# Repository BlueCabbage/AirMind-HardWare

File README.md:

Hardware
========

PX4 Hardware designs

Website at: http://pixhawk.org

PX4 is an open hardware design, following the OSHW 1.1 definition licensed under the Creative Commons Attribution-ShareAlike 3.0 Unported (CC BY-SA 3.0) license.

Pull requests for relevant fixes are very welcome.

Pixhawk v1 Hardware
===================

FMUv1 & FMUv2 boards

Design files are EAGLE CAD files (can be viewed with the free version)
www.cadsoftusa.com/

And BOM management is performed using Bob Starr's BOM-EX plugin:
http://www.bobstarr.net/pages/downloads.html

Pixhawk v2 Hardware
===================

FMUv3 board (and IMUv3 + PSMv3 support components)

The Pixhawk v2 Hardware is the result of a collaboration of the open hardware development community and 3D Robotics and has been designed in Altium.

MindPX V2 Hardware
===================

MindPX V2 board (Hardware version:   v2.2)
http://www.mindpx.net

Product brief:
http://www.mindpx.net/assets/accessories/brochure.pdf

Hardware specification:
http://www.mindpx.net/assets/accessories/Specification_MindPX.pdf

User manual:
http://www.mindpx.net/assets/accessories/UserGuide_MindPX.pdf

Revisions against Pixhawk:

1. 6 PWM distance sensors inputs
2. 1 extra parallel I2C port (so can support external compass and px4flow simultaneously)
3. Secondary USB port  for companion computer (converted from UART2 using onboard CP2104)
4. exposed SWD debug port
5. Built-in vibration dampening, support hard mount on air frames.
6. removed in v2.2:
        • Spektrum DSM / DSM2 / DSM-X® Satellite compatible input
        • Futaba S.BUS® compatible input and output
        • auxiliary outputs
        • safety switch (moved to power distribution board as eSwitch)

Note: MindPX v2.2 supports maximum 6 direct PWM outputs.

Creative Commons License Disclaimer
===================================

UNLESS OTHERWISE MUTUALLY AGREED TO BY THE PARTIES IN WRITING, LICENSOR OFFERS THE WORK AS-IS AND MAKES NO REPRESENTATIONS OR WARRANTIES OF ANY KIND CONCERNING THE WORK, EXPRESS, IMPLIED, STATUTORY OR OTHERWISE, INCLUDING, WITHOUT LIMITATION, WARRANTIES OF TITLE, MERCHANTIBILITY, FITNESS FOR A PARTICULAR PURPOSE, NONINFRINGEMENT, OR THE ABSENCE OF LATENT OR OTHER DEFECTS, ACCURACY, OR THE PRESENCE OF ABSENCE OF ERRORS, WHETHER OR NOT DISCOVERABLE. SOME JURISDICTIONS DO NOT ALLOW THE EXCLUSION OF IMPLIED WARRANTIES, SO SUCH EXCLUSION MAY NOT APPLY TO YOU.
EXCEPT TO THE EXTENT REQUIRED BY APPLICABLE LAW, IN NO EVENT WILL LICENSOR BE LIABLE TO YOU ON ANY LEGAL THEORY FOR ANY SPECIAL, INCIDENTAL, CONSEQUENTIAL, PUNITIVE OR EXEMPLARY DAMAGES ARISING OUT OF THIS LICENSE OR THE USE OF THE WORK, EVEN IF LICENSOR HAS BEEN ADVISED OF THE POSSIBILITY OF SUCH DAMAGES.

http://creativecommons.org/licenses/by-sa/3.0/

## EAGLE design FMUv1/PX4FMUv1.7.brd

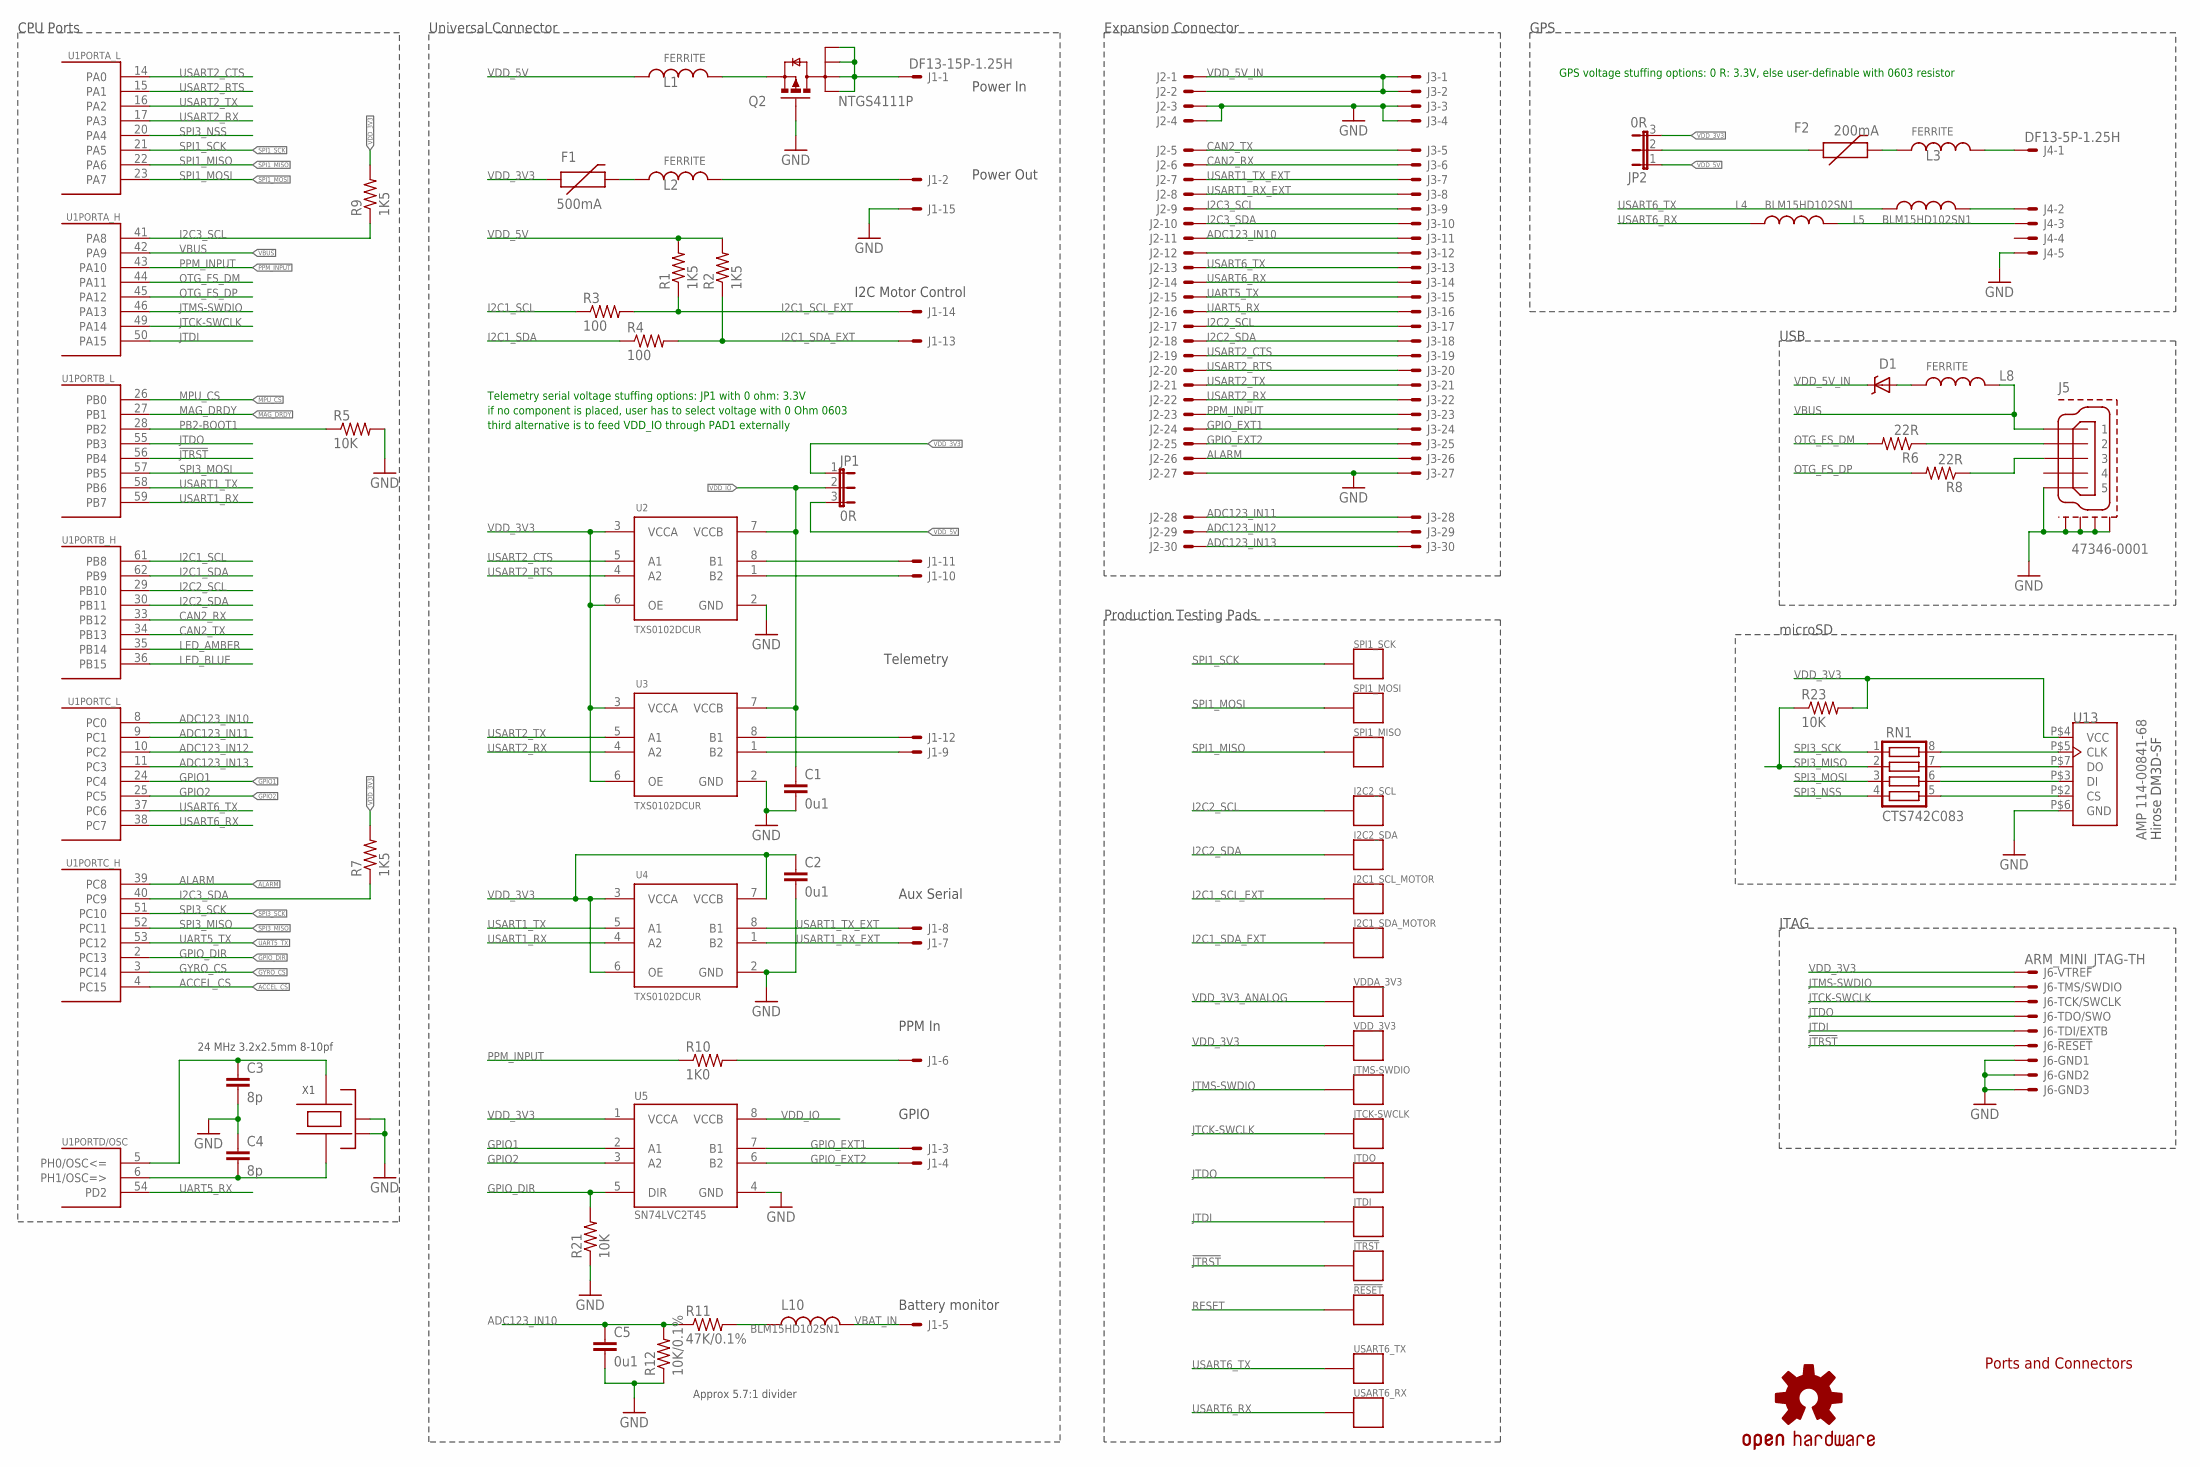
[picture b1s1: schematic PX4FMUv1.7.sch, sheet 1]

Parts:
!JTRST: PAD.04; PAD.04X.04; PARTNO *
!RESET: PAD.04; PAD.04X.04; PARTNO *
C1, C2, C5: 0u1; 0402-CAP; PARTNO CC0402ZRY5V7BB104
C3, C4: 8p; 0402-CAP; PARTNO C1005C0G1H080C
D1: MSS1P4-M3; MICROSMP; PARTNO MSS1P4-M3/89A
F1: 500mA; 0402-PTC; PARTNO MF-FSMF050X-2
F2: 200mA; 0402-PTC; PARTNO MF-FSMF020X-2
I2C1_SCL_MOTOR, I2C1_SDA_MOTOR, I2C2_SCL: PAD.03; PAD.03X.03; PARTNO *
I2C2_SDA: PAD.04; PAD.04X.04; PARTNO *
J1: DF13-15P-1.25H; DF13A-15P-1.25H; PARTNO DF13A-15P-1.25H(20)
J2: HEADER_2X15-REV; HEADER_2MM_2X15_REVERSE; PARTNO 953230-2000-AR-PR
J3: HEADER_2X15; HEADER_2MM_2X15; PARTNO 953230-2000-AR-PR
J4: DF13-5P-1.25H; DF13A-5P-1.25H; PARTNO DF13A-5P-1.25H(20)
J5: 47346-0001; MOLEX-47346-0001; PARTNO 47346-0001
J6: ARM_MINI_JTAG-TH; FTSH-105-01-XXX-DV; PARTNO M50-3900542
JP1, JP2: 0R; SJ_3_0603_PASTE1&2; PARTNO RMCF0402ZT0R00
JTCK-SWCLK: PAD.04; PAD.04X.04; PARTNO *
JTDI: PAD.04; PAD.04X.04; PARTNO *
JTDO: PAD.04; PAD.04X.04; PARTNO *
JTMS-SWDIO: PAD.04; PAD.04X.04; PARTNO *
L1, L2, L3, L8: FERRITE; 0402-IND; PARTNO BKP1005HS121-T
L4, L5, L10: BLM15HD102SN1; 0402-IND; PARTNO BLM15HD102SN1
Q2: NTGS4111P; TSOP-6; PARTNO NTGS4111P
R1, R2, R7, R9: 1K5; 0402-RES; PARTNO RMCF0402JT1K50
R3, R4: 100; 0402-RES; PARTNO RMCF0402JT100R
R5, R21, R23: 10K; 0402-RES; PARTNO RMCF0402FT10K0
R6, R8: 22R; 0402-RES; PARTNO RMCF0402JT22R0
R10: 1K0; 0402-RES; PARTNO RMCF0402JT1K00
R11: 47K/0.1%; 0402-RES; PARTNO ERA-2AEB473X
R12: 10K/0.1%; 0402-RES; PARTNO ERA-2AEB103X
RN1: CTS742C083; PARTNO TC164-JR-07100RL
SPI1_MISO, SPI1_MOSI, SPI1_SCK: PAD.04; PAD.04X.04; PARTNO *
U1: STM32F405RGT6; TQFP64; PARTNO STM32F405RGT6
U2, U3, U4: TXS0102DCUR; TI-DCU; PARTNO TXS0102DCUR
U5: SN74LVC2T45; TI-DCU; PARTNO SN74LVC2T45
U13: AMP 114-00841-68; AMPHENOL_114-00841-68; PARTNO 114-00841-68
U$7: OSHW-LOGOS; OSHW-LOGO-S; PARTNO *
USART6_RX, USART6_TX: PAD.04; PAD.04X.04; PARTNO *
VDDA_3V3: PAD.04; PAD.04X.04; PARTNO *
VDD_3V3: PAD.04; PAD.04X.04; PARTNO *
X1: 24 MHz 3.2x2.5mm 8-10pf; OSCILLATOR-3.2X2.5; PARTNO NX3225SA-24.000000MHZ

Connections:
!JTRST: !JTRST.P$1, J6.10, U1.56 (PB4)
ACCEL_CS: U1.4 (PC15); also elsewhere on the board
ADC123_IN10: C5.1, J2.11, J3.11, R11.1, R12.2, U1.8 (PC0)
ADC123_IN11: J2.28, J3.28, U1.9 (PC1)
ADC123_IN12: J2.29, J3.29, U1.10 (PC2)
ADC123_IN13: J2.30, J3.30, U1.11 (PC3); also elsewhere on the board
ALARM: J2.26, J3.26, U1.39 (PC8); also elsewhere on the board
CAN2_RX: J2.6, J3.6, U1.33 (PB12)
CAN2_TX: J2.5, J3.5, U1.34 (PB13)
GND: C1.2, C2.2, C3.2, C4.1, C5.2, J1.15, J2.3, J2.4, J2.27, J3.3, J3.4, J3.27, J4.5, J5.GND (5), J5.GND1, J5.GND2, J5.GND3, J5.GND4, J6.3, J6.5, J6.9, Q2.3 (G), R5.2, R12.1, R21.1, U2.2 (GND), U3.2 (GND), U4.2 (GND), U5.4 (GND), U13.P$6 (GND), X1.2 (NC_2), X1.4 (NC_4); also elsewhere on the board
GPIO1: U1.24 (PC4), U5.2 (A1)
GPIO2: U1.25 (PC5), U5.3 (A2)
GPIO_DIR: R21.2, U1.2 (PC13), U5.5 (DIR)
GPIO_EXT1: J1.3, J2.24, J3.24, U5.7 (B1)
GPIO_EXT2: J1.4, J2.25, J3.25, U5.6 (B2)
GYRO_CS: U1.3 (PC14); also elsewhere on the board
I2C1_SCL: R3.1, U1.61 (PB8)
I2C1_SCL_EXT: I2C1_SCL_MOTOR.P$1, J1.14, R1.1, R3.2
I2C1_SDA: R4.1, U1.62 (PB9)
I2C1_SDA_EXT: I2C1_SDA_MOTOR.P$1, J1.13, R2.1, R4.2
I2C2_SCL: I2C2_SCL.P$1, J2.17, J3.17, U1.29 (PB10); also elsewhere on the board
I2C2_SDA: I2C2_SDA.P$1, J2.18, J3.18, U1.30 (PB11); also elsewhere on the board
I2C3_SCL: J2.9, J3.9, R9.1, U1.41 (PA8)
I2C3_SDA: J2.10, J3.10, R7.1, U1.40 (PC9)
JTCK-SWCLK: J6.4, JTCK-SWCLK.P$1, U1.49 (PA14)
JTDI: J6.8, JTDI.P$1, U1.50 (PA15)
JTDO: J6.6, JTDO.P$1, U1.55 (PB3)
JTMS-SWDIO: J6.2, JTMS-SWDIO.P$1, U1.46 (PA13)
LED_AMBER: U1.35 (PB14); also elsewhere on the board
LED_BLUE: U1.36 (PB15); also elsewhere on the board
MAG_DRDY: U1.27 (PB1); also elsewhere on the board
MPU_CS: U1.26 (PB0); also elsewhere on the board
unnamed: C4.2, U1.6 (PH1/OSC=>), X1.1
unnamed: C3.1, U1.5 (PH0/OSC<=), X1.3
unnamed: J1.2, L2.2
unnamed: F2.2, L3.1
unnamed: J4.2, L5.2
unnamed: J4.3, L4.2
unnamed: J1.11, U2.8 (B1)
unnamed: J1.10, U2.1 (B2)
unnamed: L1.2, Q2.4 (S)
unnamed: J1.12, U3.8 (B1)
unnamed: J1.9, U3.1 (B2)
unnamed: F2.1, JP2.2
unnamed: J2.12, J3.12
unnamed: RN1.5, U13.P$2 (CS)
unnamed: D1.ANODE (A), L8.1
unnamed: J4.1, L3.2
unnamed: RN1.6, U13.P$3 (DI)
unnamed: F1.2, L2.1
unnamed: RN1.7, U13.P$7 (DO)
unnamed: RN1.8, U13.P$5 (CLK)
unnamed: L10.1, R11.2
unnamed: J1.1, Q2.1 (D), Q2.2 (D1), Q2.5 (D2), Q2.6 (D3)
OTG_DM: J5.D- (2), R6.1
OTG_DP: J5.D+ (3), R8.1
OTG_FS_DM: R6.2, U1.44 (PA11)
OTG_FS_DP: R8.2, U1.45 (PA12)
PB2-BOOT1: R5.1, U1.28 (PB2)
PPM_INPUT: J2.23, J3.23, R10.1, U1.43 (PA10)
PPM_INPUT_CON: J1.6, R10.2
RESET: !RESET.P$1; also elsewhere on the board
SPI1_MISO: SPI1_MISO.P$1, U1.22 (PA6); also elsewhere on the board
SPI1_MOSI: SPI1_MOSI.P$1, U1.23 (PA7); also elsewhere on the board
SPI1_SCK: SPI1_SCK.P$1, U1.21 (PA5); also elsewhere on the board
SPI3_MISO: R23.1, RN1.2, U1.52 (PC11)
SPI3_MOSI: RN1.3, U1.57 (PB5)
SPI3_NSS: RN1.4, U1.20 (PA4)
SPI3_SCK: RN1.1, U1.51 (PC10)
UART5_RX: J2.16, J3.16, U1.54 (PD2)
UART5_TX: J2.15, J3.15, U1.53 (PC12)
USART1_RX: U1.59 (PB7), U4.4 (A2)
USART1_RX_EXT: J1.7, J2.8, J3.8, U4.1 (B2)
USART1_TX: U1.58 (PB6), U4.5 (A1)
USART1_TX_EXT: J1.8, J2.7, J3.7, U4.8 (B1)
USART2_CTS: J2.19, J3.19, U1.14 (PA0), U2.5 (A1)
USART2_RTS: J2.20, J3.20, U1.15 (PA1), U2.4 (A2)
USART2_RX: J2.22, J3.22, U1.17 (PA3), U3.4 (A2)
USART2_TX: J2.21, J3.21, U1.16 (PA2), U3.5 (A1)
USART6_RX: J2.14, J3.14, L4.1, U1.38 (PC7), USART6_RX.P$1
USART6_TX: J2.13, J3.13, L5.1, U1.37 (PC6), USART6_TX.P$1
VBAT_IN: J1.5, L10.2; also elsewhere on the board
VBUS: J5.VBUS (1), L8.2, U1.42 (PA9)
VDD_3V3: C2.1, F1.1, J6.1, JP1.1, JP2.3, R7.2, R9.2, R23.2, U2.3 (VCCA), U2.6 (OE), U3.3 (VCCA), U3.6 (OE), U4.3 (VCCA), U4.6 (OE), U4.7 (VCCB), U5.1 (VCCA), U13.P$4 (VCC), VDD_3V3.P$1; also elsewhere on the board
VDD_3V3_ANALOG: VDDA_3V3.P$1; also elsewhere on the board
VDD_5V: JP1.3, JP2.1, L1.1, R1.2, R2.2; also elsewhere on the board
VDD_5V_IN: D1.CATHODE (C), J2.1, J2.2, J3.1, J3.2; also elsewhere on the board
VDD_IO: C1.1, JP1.2, U2.7 (VCCB), U3.7 (VCCB), U5.8 (VCCB)

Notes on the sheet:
Ports and Connectors
Telemetry
I2C Motor Control
Power In
Battery monitor
GPIO
Approx 5.7:1 divider
CPU Ports
Universal Connector
GPS
USB
JTAG
GPS voltage stuffing options: 0 R: 3.3V, else user-definable with 0603 resistor
Telemetry serial voltage stuffing options: JP1 with 0 ohm: 3.3V
Aux Serial
PPM In
Expansion Connector
if no component is placed, user has to select voltage with 0 Ohm 0603
Production Testing Pads
Power Out
microSD
third alternative is to feed VDD_IO through PAD1 externally
Hirose DM3D-SF

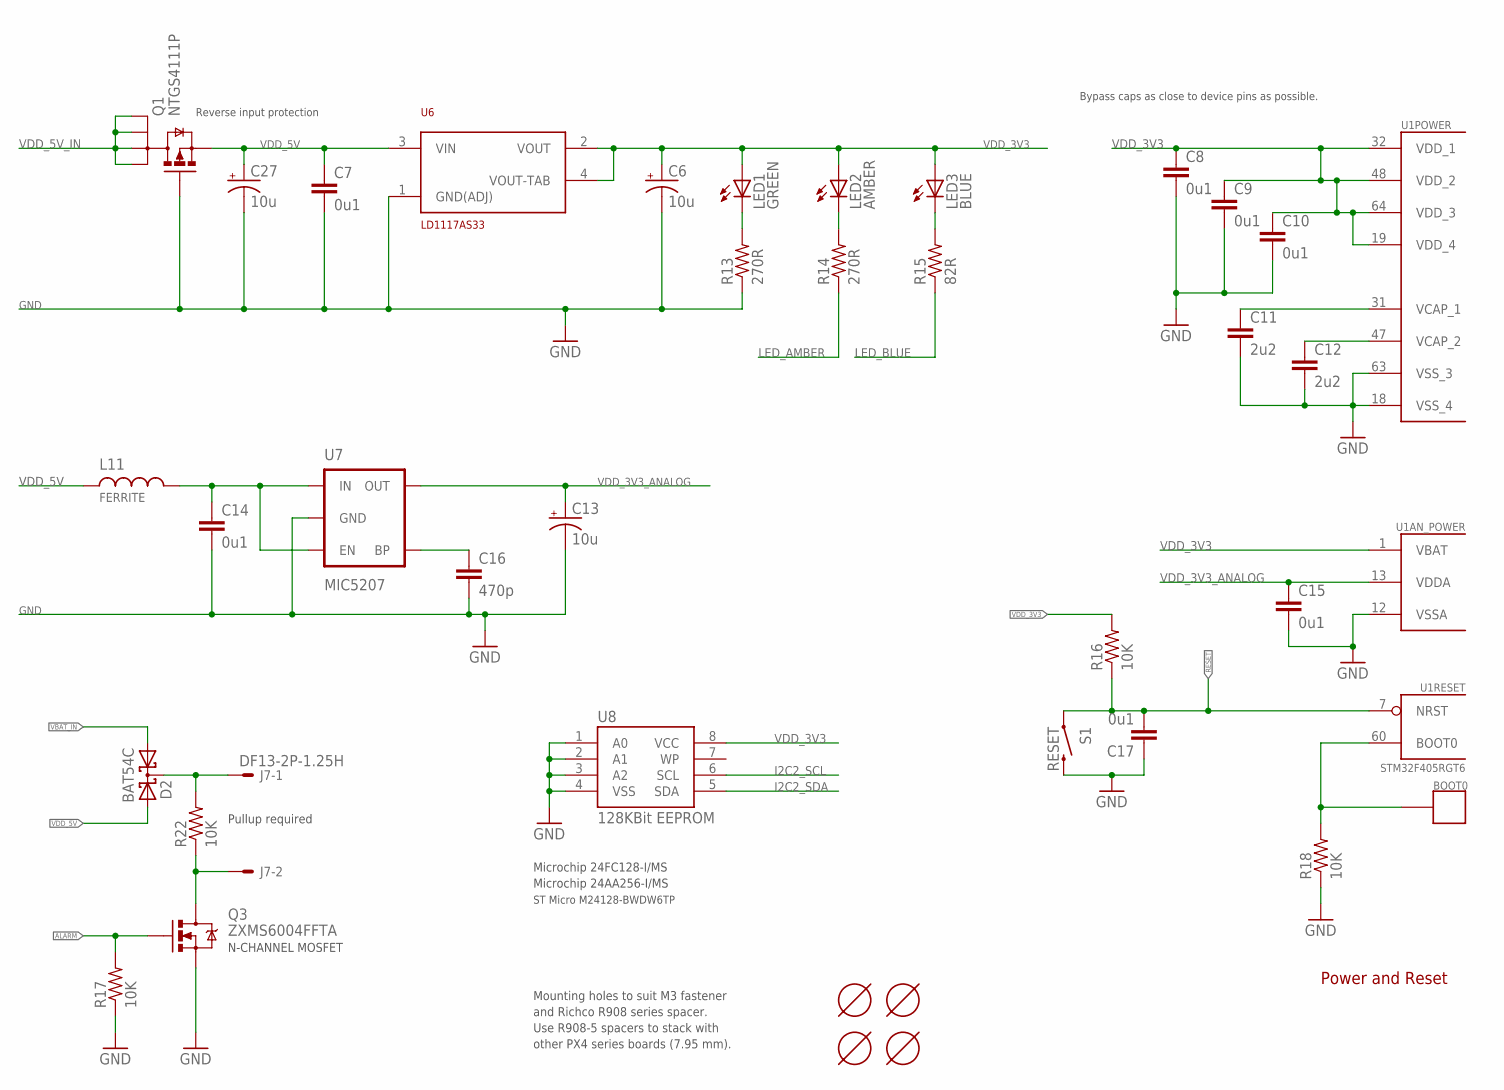
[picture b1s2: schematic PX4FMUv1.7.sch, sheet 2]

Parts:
BOOT0: PAD.04; PAD.04X.04; PARTNO *
C6, C13, C27: 10u; EIA3216; PARTNO F931A106MAA
C7, C8, C9, C10, C14, C15, C17: 0u1; 0402-CAP; PARTNO CC0402ZRY5V7BB104
C11, C12: 2u2; 0402-CAP; PARTNO C1608Y5V1C225Z
C16: 470p; 0402-CAP; PARTNO CC0402KRX7R9BB471
D2: BAT54C; SOT23-3; PARTNO BAT54C-7-F
J7: DF13-2P-1.25H; DF13A-2P-1.25H; PARTNO DF13-2P-1.25H(20)
L11: FERRITE; 0402-IND; PARTNO BKP1005HS121-T
LED1: GREEN; LED-0603; PARTNO LNJ337W83RA
LED2: AMBER; LED-0603; PARTNO LNJ437W84RA
LED3: BLUE; LED-0603; PARTNO LNJ937W8CRA
Q1: NTGS4111P; TSOP-6; PARTNO NTGS4111P
Q3: ZXMS6004FFTA; SOT23-3; PARTNO ZXMS6004FFTA
R13, R14: 270R; 0402-RES; PARTNO RC0402JR-07270RL
R15: 82R; 0402-RES; PARTNO RC0402JR-0782RL
R16, R17, R18, R22: 10K; 0402-RES; PARTNO RMCF0402FT10K0
S1: RESET; EVQP7J01K; PARTNO EVQP7J01K
U1: STM32F405RGT6; TQFP64; PARTNO STM32F405RGT6
U6: LD1117AS33; SOT-223; PARTNO LD1117AS33
U7: MIC5207; SOT23-5; PARTNO MIC5207-3.3YM5
U8: 128KBit EEPROM; MSOP-8; PARTNO 24FC128-I/MS
U$1, U$2, U$3, U$4: MOUNT-HOLE3.1MM; MOUNT-HOLE3.1; PARTNO *

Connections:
ALARM: Q3.1 (G), R17.2; also elsewhere on the board
BOOT0: BOOT0.P$1, R18.2, U1.60 (BOOT0)
GND: C6.C (-), C7.2, C8.2, C9.2, C10.2, C11.2, C12.2, C13.C (-), C14.2, C15.2, C16.2, C17.1, C27.C (-), Q1.3 (G), Q3.2 (S), R13.1, R17.1, R18.1, S1.B3 (2), U1.12 (VSSA), U1.18 (VSS_4), U1.63 (VSS_3), U6.1 (GND(ADJ)), U7.2 (GND), U8.1 (A0), U8.2 (A1), U8.3 (A2), U8.4 (VSS); also elsewhere on the board
I2C2_SCL: U8.6 (SCL); also elsewhere on the board
I2C2_SDA: U8.5 (SDA); also elsewhere on the board
LED_AMBER: R14.1; also elsewhere on the board
LED_BLUE: R15.1; also elsewhere on the board
unnamed: D2.3 (CC), J7.1, R22.2
unnamed: C16.1, U7.4 (BP)
unnamed: J7.2, Q3.3 (D), R22.1
unnamed: LED3.C, R15.2
unnamed: LED1.C, R13.2
unnamed: LED2.C, R14.2
unnamed: C14.1, L11.2, U7.1 (IN), U7.3 (EN)
RESET: C17.2, R16.1, S1.A1 (1), U1.7 (NRST); also elsewhere on the board
VBAT_IN: D2.1 (A1); also elsewhere on the board
VCAP_1: C11.1, U1.31 (VCAP_1)
VCAP_2: C12.1, U1.47 (VCAP_2)
VDD_3V3: C6.A (+), C8.1, C9.1, C10.1, LED1.A, LED2.A, LED3.A, R16.2, U1.1 (VBAT), U1.19 (VDD_4), U1.32 (VDD_1), U1.48 (VDD_2), U1.64 (VDD_3), U6.2 (VOUT), U6.4 (VOUT-TAB), U8.8 (VCC); also elsewhere on the board
VDD_3V3_ANALOG: C13.A (+), C15.1, U1.13 (VDDA), U7.5 (OUT); also elsewhere on the board
VDD_5V: C7.1, C27.A (+), D2.2 (A2), L11.1, Q1.4 (S), U6.3 (VIN); also elsewhere on the board
VDD_5V_IN: Q1.1 (D), Q1.2 (D1), Q1.5 (D2), Q1.6 (D3); also elsewhere on the board

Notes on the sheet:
Power and Reset
Bypass caps as close to device pins as possible.
Microchip 24FC128-I/MS
Microchip 24AA256-I/MS
Mounting holes to suit M3 fastener
and Richco R908 series spacer.
ST Micro M24128-BWDW6TP
Reverse input protection
N-CHANNEL MOSFET
Pullup required
Use R908-5 spacers to stack with
other PX4 series boards (7.95 mm).

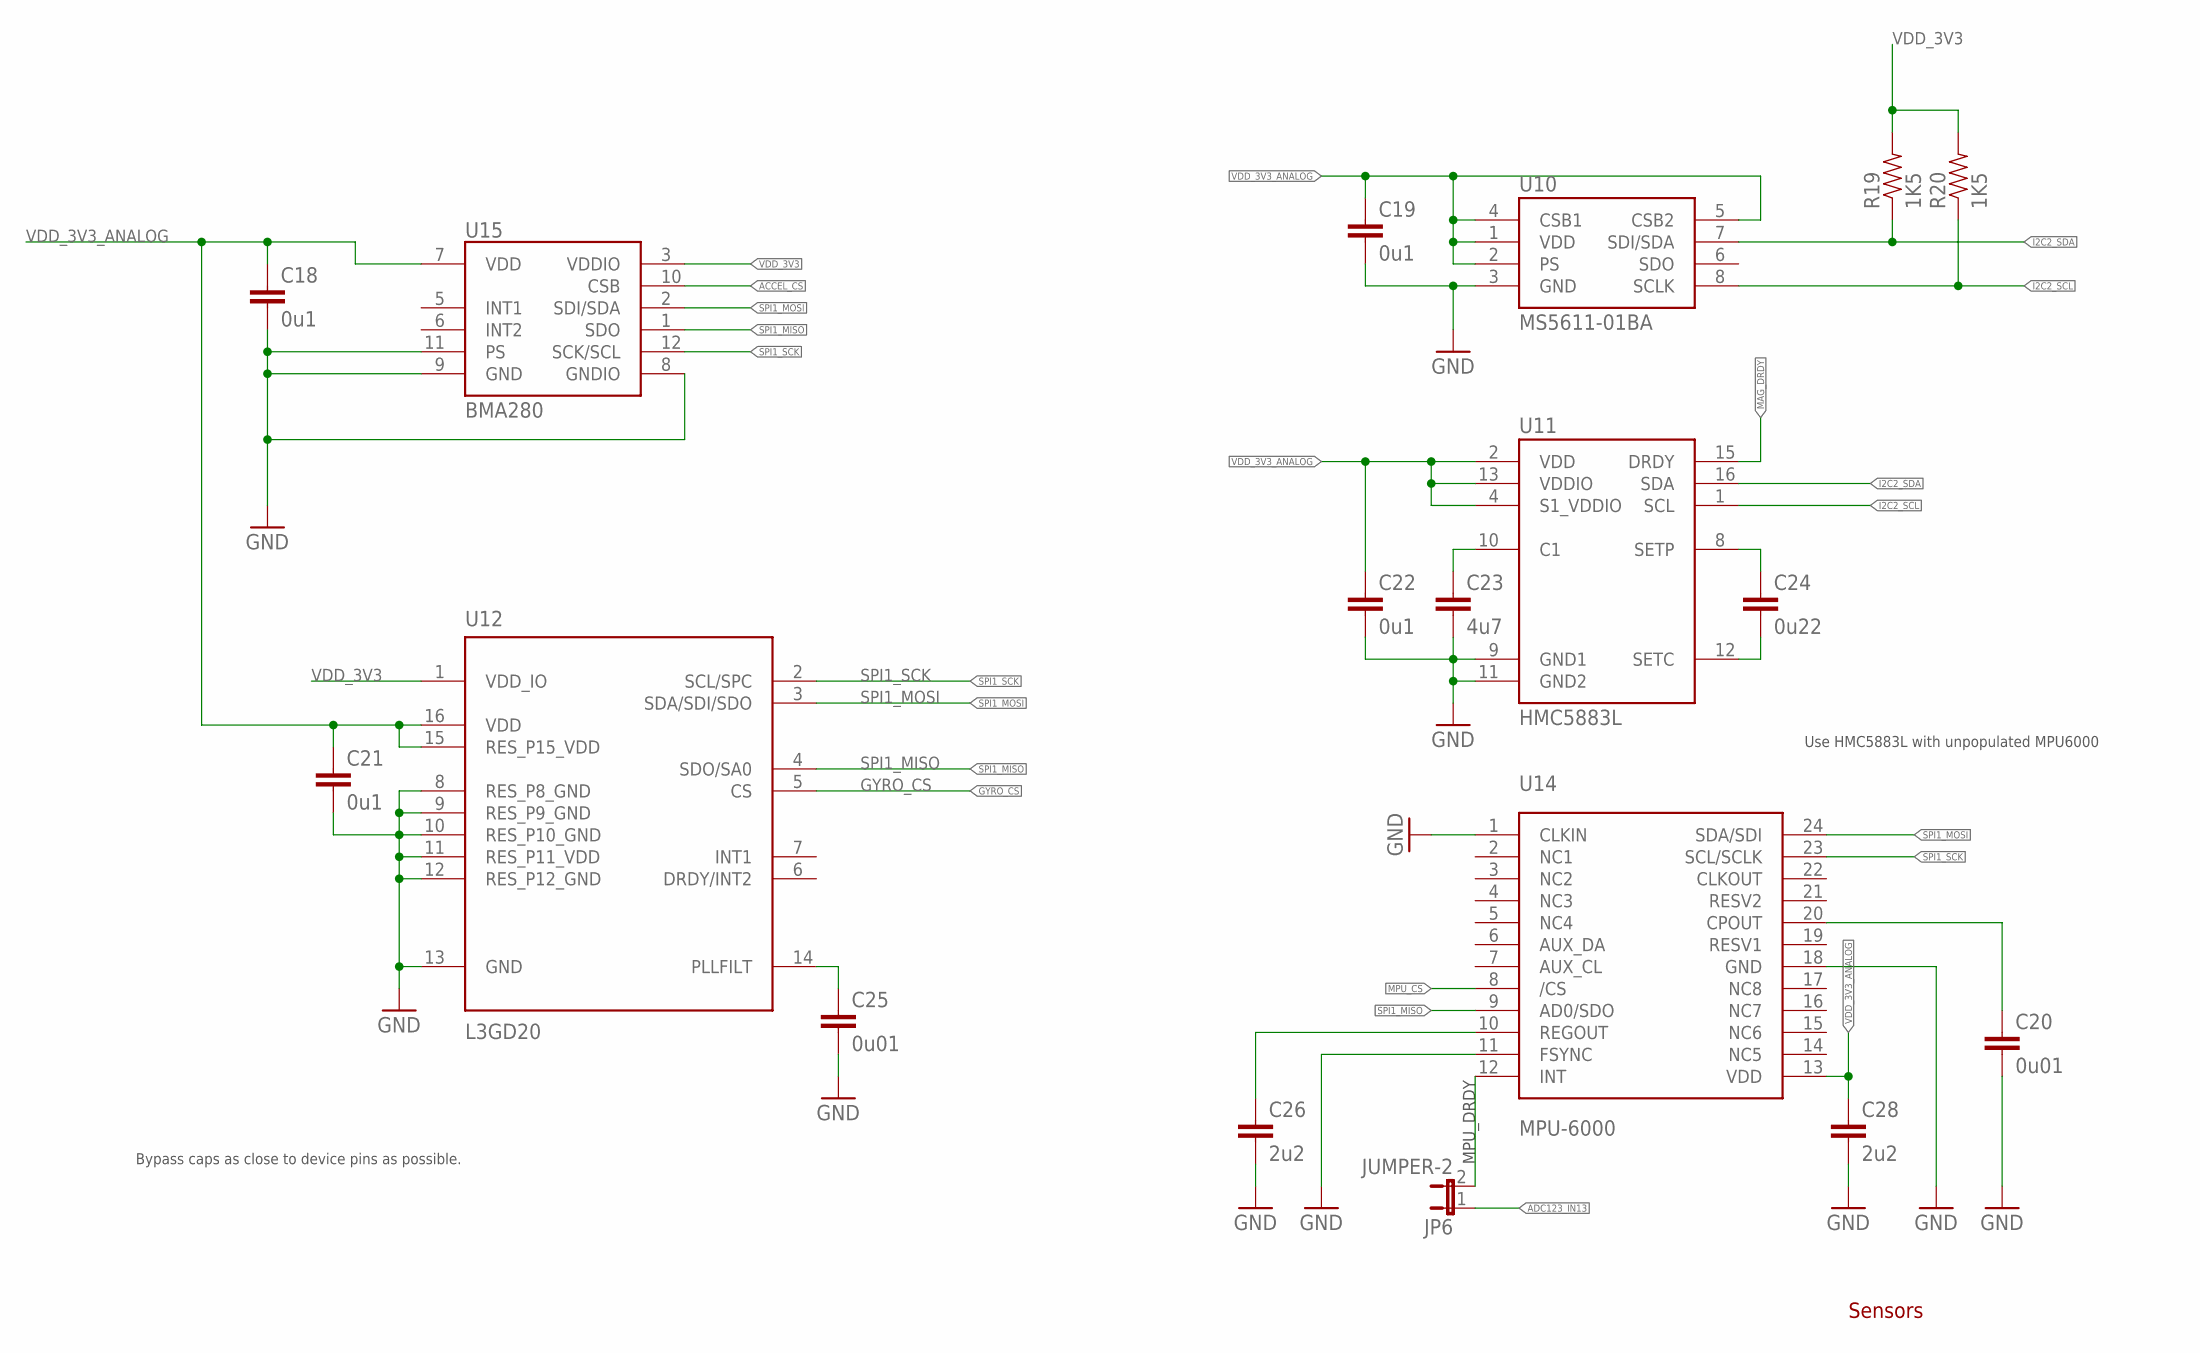
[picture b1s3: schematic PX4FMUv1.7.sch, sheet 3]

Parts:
C18, C19, C21, C22: 0u1; 0402-CAP; PARTNO CC0402ZRY5V7BB104
C20, C25: 0u01; 0402-CAP; PARTNO CC0402KRX7R7BB103
C23: 4u7; 0402-CAP; PARTNO C1608Y5V0J475Z
C24: 0u22; 0402-CAP; PARTNO C1005Y5V1C224Z
C26, C28: 2u2; 0402-CAP; PARTNO C1608Y5V1C225Z
JP6: JUMPER-2; SJ_2
R19, R20: 1K5; 0402-RES; PARTNO RMCF0402JT1K50
U10: MS5611-01BA; PARTNO MS5611-01BA
U11: HMC5883L; HMC5883L-MAN; PARTNO HMC5883L
U12: L3GD20; L3G4200DH-MAN; PARTNO L3GD20
U14: MPU-6000; QFN-24; PARTNO MPU-6000
U15: BMA280; PARTNO *

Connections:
ACCEL_CS: U15.10 (CSB); also elsewhere on the board
ADC123_IN13: JP6.1; also elsewhere on the board
GND: C18.2, C19.2, C20.2, C21.2, C22.2, C23.2, C25.2, C26.2, C28.2, U10.3 (GND), U11.9 (GND1), U11.11 (GND2), U12.8 (RES_P8_GND), U12.9 (RES_P9_GND), U12.10 (RES_P10_GND), U12.11 (RES_P11_VDD), U12.12 (RES_P12_GND), U12.13 (GND), U14.1 (CLKIN), U14.11 (FSYNC), U14.18 (GND), U15.8 (GNDIO), U15.9 (GND), U15.11 (PS); also elsewhere on the board
GYRO_CS: U12.5 (CS); also elsewhere on the board
I2C2_SCL: R20.1, U10.8 (SCLK), U11.1 (SCL); also elsewhere on the board
I2C2_SDA: R19.1, U10.7 (SDI/SDA), U11.16 (SDA); also elsewhere on the board
MAG_DRDY: U11.15 (DRDY); also elsewhere on the board
MPU_CS: U14.8 (/CS); also elsewhere on the board
unnamed: C24.1, U11.8 (SETP)
unnamed: C24.2, U11.12 (SETC)
unnamed: C25.1, U12.14 (PLLFILT)
unnamed: C23.1, U11.10 (C1)
unnamed: C20.1, U14.20 (CPOUT)
unnamed: C26.1, U14.10 (REGOUT)
unnamed: JP6.2, U14.12 (INT)
SPI1_MISO: U12.4 (SDO/SA0), U14.9 (AD0/SDO), U15.1 (SDO); also elsewhere on the board
SPI1_MOSI: U12.3 (SDA/SDI/SDO), U14.24 (SDA/SDI), U15.2 (SDI/SDA); also elsewhere on the board
SPI1_SCK: U12.2 (SCL/SPC), U14.23 (SCL/SCLK), U15.12 (SCK/SCL); also elsewhere on the board
VDD_3V3: R19.2, R20.2, U12.1 (VDD_IO), U15.3 (VDDIO); also elsewhere on the board
VDD_3V3_ANALOG: C18.1, C19.1, C21.1, C22.1, C28.1, U10.1 (VDD), U10.2 (PS), U10.4 (CSB1), U10.5 (CSB2), U11.2 (VDD), U11.4 (S1_VDDIO), U11.13 (VDDIO), U12.15 (RES_P15_VDD), U12.16 (VDD), U14.13 (VDD), U15.7 (VDD); also elsewhere on the board

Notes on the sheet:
Sensors
Bypass caps as close to device pins as possible.
Use HMC5883L with unpopulated MPU6000
MPU_DRDY

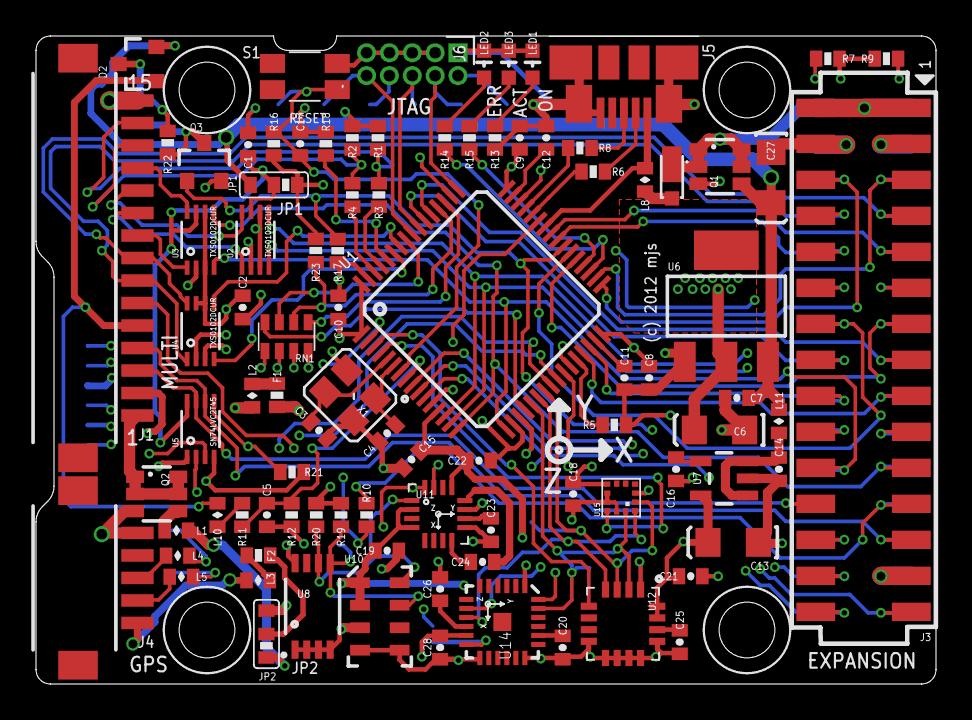
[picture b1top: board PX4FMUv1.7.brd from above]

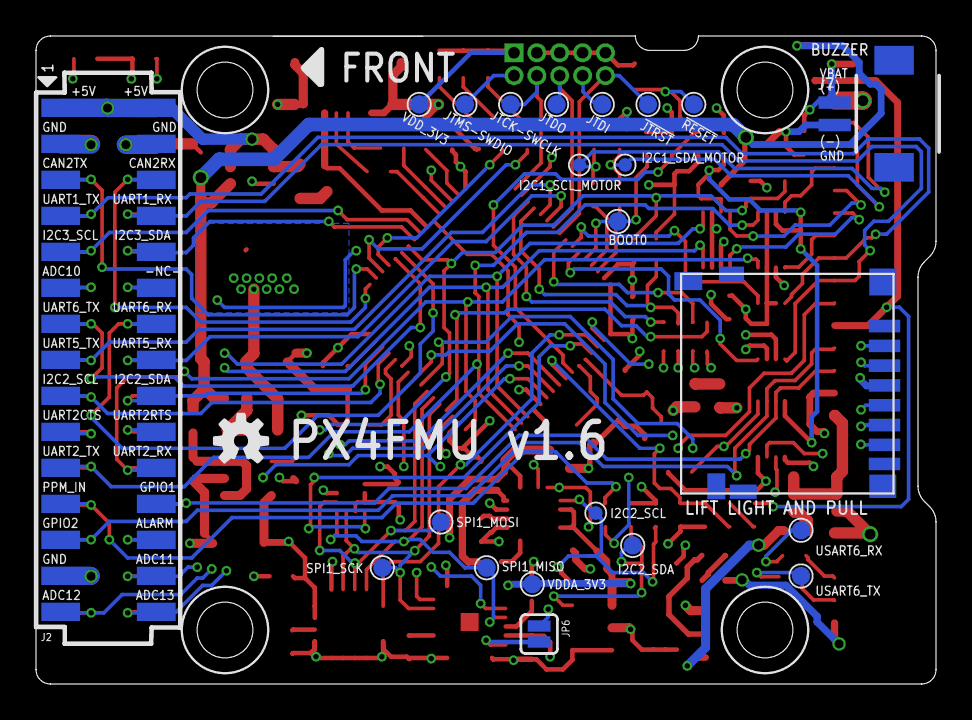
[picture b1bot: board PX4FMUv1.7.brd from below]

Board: 4 copper layers, 50.0 x 36.0 mm, 119 parts (23 on the bottom side), 105 nets.

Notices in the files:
FMUv1/PX4FMUv1.7.brd:
(c) 2012 mjs
FMUv2/PX4FMUv2.4.6.brd:
(c) 2013 mjs/lm/jo
